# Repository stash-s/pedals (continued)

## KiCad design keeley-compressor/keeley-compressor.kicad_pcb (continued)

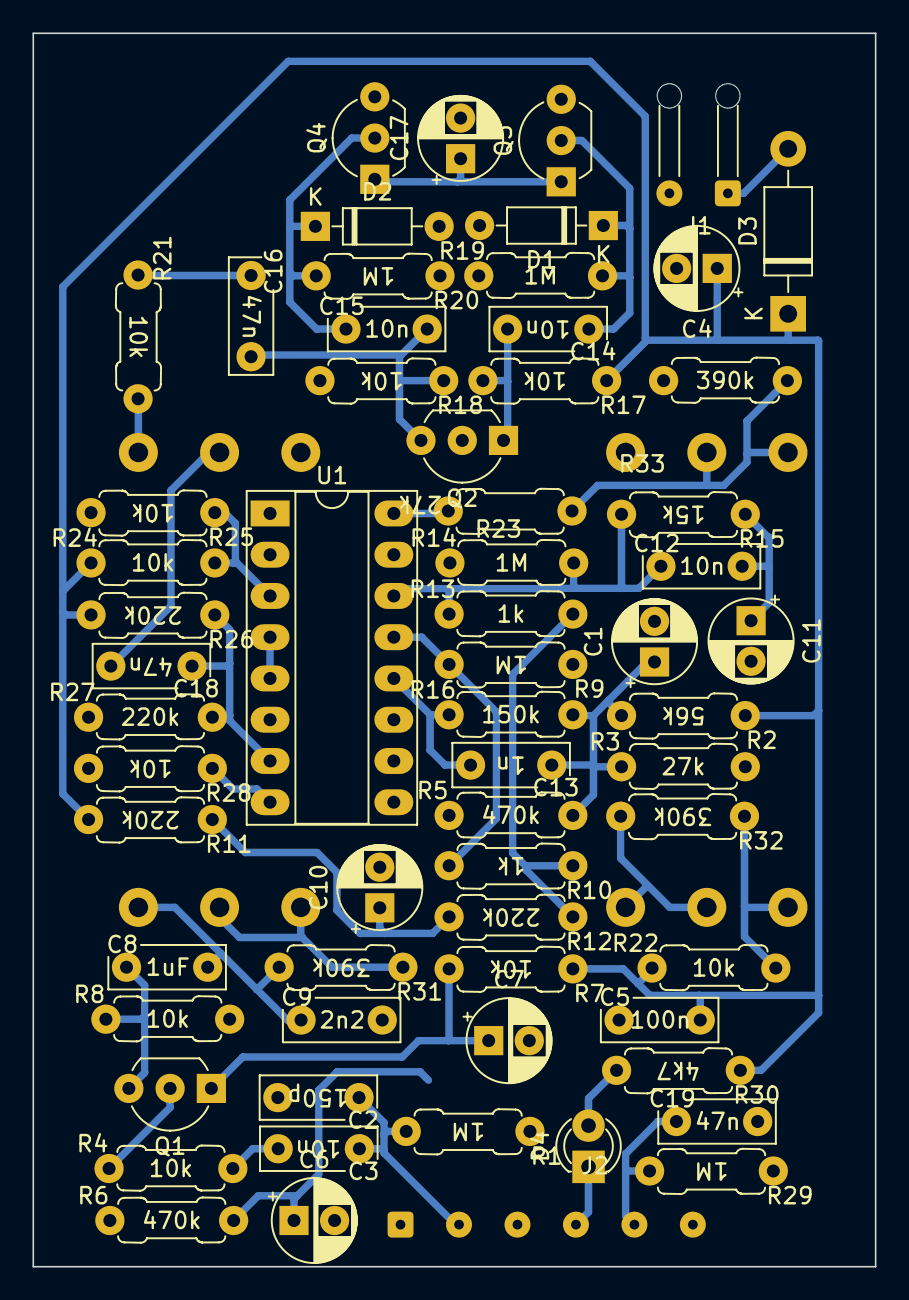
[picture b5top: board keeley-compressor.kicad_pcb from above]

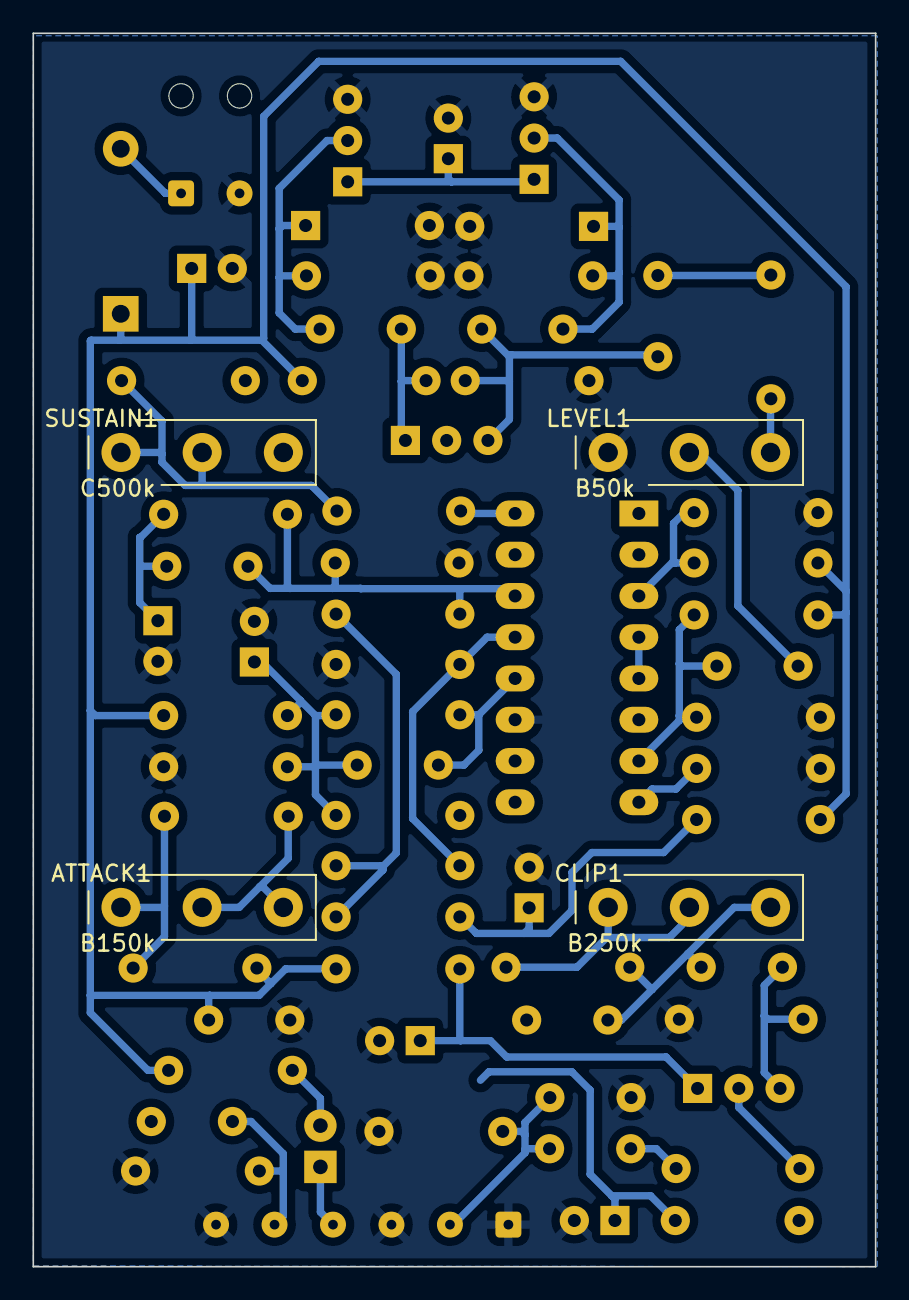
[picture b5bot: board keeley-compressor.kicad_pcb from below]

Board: 2 copper layers, 51.9 x 75.9 mm, 67 parts (4 on the bottom side), 36 nets.

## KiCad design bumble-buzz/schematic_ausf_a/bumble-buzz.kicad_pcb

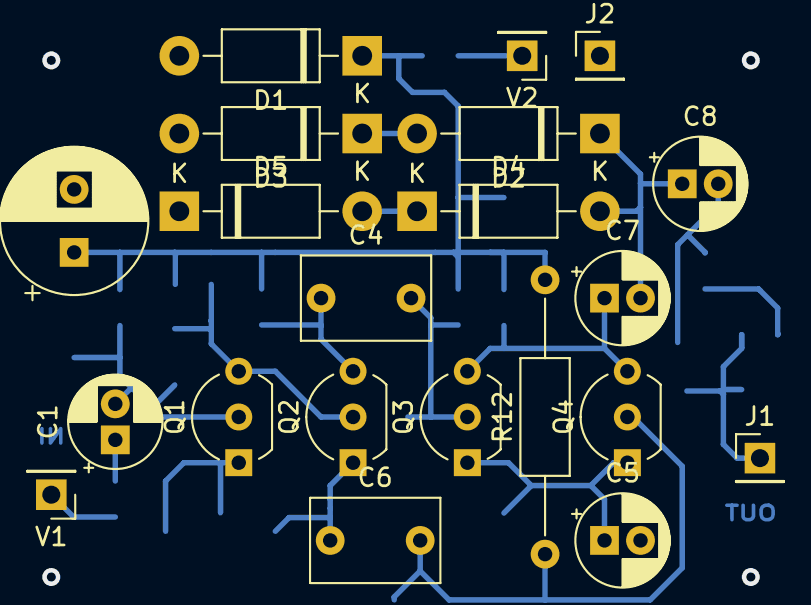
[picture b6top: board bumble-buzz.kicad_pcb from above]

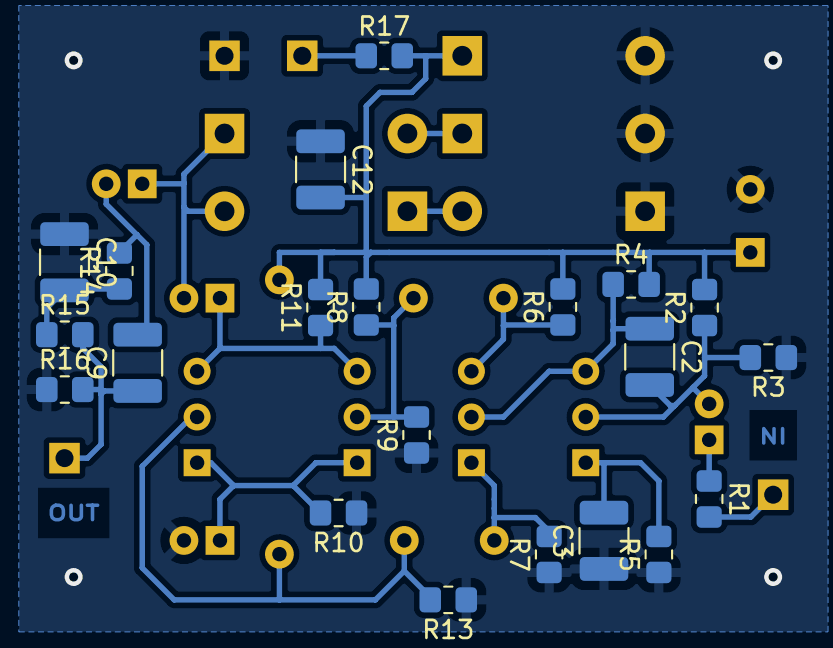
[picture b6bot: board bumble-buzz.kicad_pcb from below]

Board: 2 copper layers, 42 parts (21 on the bottom side), 20 nets.

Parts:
C1, C5, C7, C8: 10u; CP_Radial_D5.0mm_P2.00mm
C2: 2.2n; C_1210_3225Metric_Pad1.33x2.70mm_HandSolder
C3, C12: 100n; C_1210_3225Metric_Pad1.33x2.70mm_HandSolder
C4, C6: 1u; C_Rect_L7.0mm_W4.5mm_P5.00mm
C9: 1n; C_1210_3225Metric_Pad1.33x2.70mm_HandSolder
C10: 22n; C_1210_3225Metric_Pad1.33x2.70mm_HandSolder
C11: 100u; CP_Radial_D8.0mm_P3.50mm
D1, D2, D3, D4, D5: 1N4007; D_DO-41_SOD81_P10.16mm_Horizontal
J1, J2: Conn_01x01_Female; PinHeader_1x01_P2.54mm_Vertical
Q1, Q2, Q3, Q4: 2N2219; TO-92_Inline_Wide
R1, R11: 22k; R_0805_2012Metric_Pad1.20x1.40mm_HandSolder
R2, R8, R14: 100k; R_0805_2012Metric_Pad1.20x1.40mm_HandSolder
R3, R6, R7, R9, R13: 10k; R_0805_2012Metric_Pad1.20x1.40mm_HandSolder
R4, R15: 47k; R_0805_2012Metric_Pad1.20x1.40mm_HandSolder
R5, R10: 1.8k; R_0805_2012Metric_Pad1.20x1.40mm_HandSolder
R12: 100k; R_Axial_DIN0207_L6.3mm_D2.5mm_P15.24mm_Horizontal
R16: 330k; R_0805_2012Metric_Pad1.20x1.40mm_HandSolder
R17: 100; R_0805_2012Metric_Pad1.20x1.40mm_HandSolder
V1, V2: VSOURCE; PinHeader_1x01_P2.54mm_Vertical

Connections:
+9V: C11.1, C12.2, D1.1, R2.2, R4.2, R6.2, R8.2, R11.2, R12.2, R17.2
GND: C3.1, C5.2, C10.1, C11.2, C12.1, D1.2, D3.2, D5.1, J2.1, R3.1, R5.1, R7.1, R9.1, R10.1, R13.1, R16.1
IN: R1.2, V1.1
MID: C7.2, C8.1, D2.1, D4.2
unnamed: C1.1, R1.1
unnamed: C1.2, C2.2, Q1.2, R2.1, R3.2
unnamed: C2.1, Q1.3, Q2.2, R4.1
unnamed: C3.2, Q1.1, R5.2
unnamed: C4.1, Q2.3, R6.1
unnamed: C4.2, Q3.2, R8.1, R9.2
unnamed: C5.1, Q3.1, Q4.1, R10.2
unnamed: C6.1, Q2.1, R7.2
unnamed: C6.2, Q4.2, R12.1, R13.2
unnamed: C7.1, Q3.3, Q4.3, R11.1
unnamed: C8.2, C9.2, R14.2
unnamed: C10.2, R14.1, R15.1
unnamed: D2.2, D3.1
unnamed: D4.1, D5.2
OUT: C9.1, J1.1, R15.2, R16.2
SUPPLY: R17.1, V2.1

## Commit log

2022-01-08 Added keeley-compressor schematic
2022-01-08 Added front and back chassis templates for PSU.
2022-01-10 Added bumble buzz schematic as built before
2022-01-19 Intermittent eng thumb redux
2022-01-23 Engineers Thumb 1st. cancdidate
2022-01-23 Resized vias.
2022-01-23 Added small imprints and generated SVG file
2022-01-30 Adding Engeeners thumb chassis decal
2022-11-16 Added compressor and psu schematics.
2022-11-16 Added compressor and PSU simmulation.
2022-11-16 Added all pedals
2022-11-16 Replace submodule with directory
